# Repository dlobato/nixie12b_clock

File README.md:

# nixie12b_clock

This is just a simple project to build a clock using nixie displays. It's kind of a prototype to play with the nixies, although it's fully functional.

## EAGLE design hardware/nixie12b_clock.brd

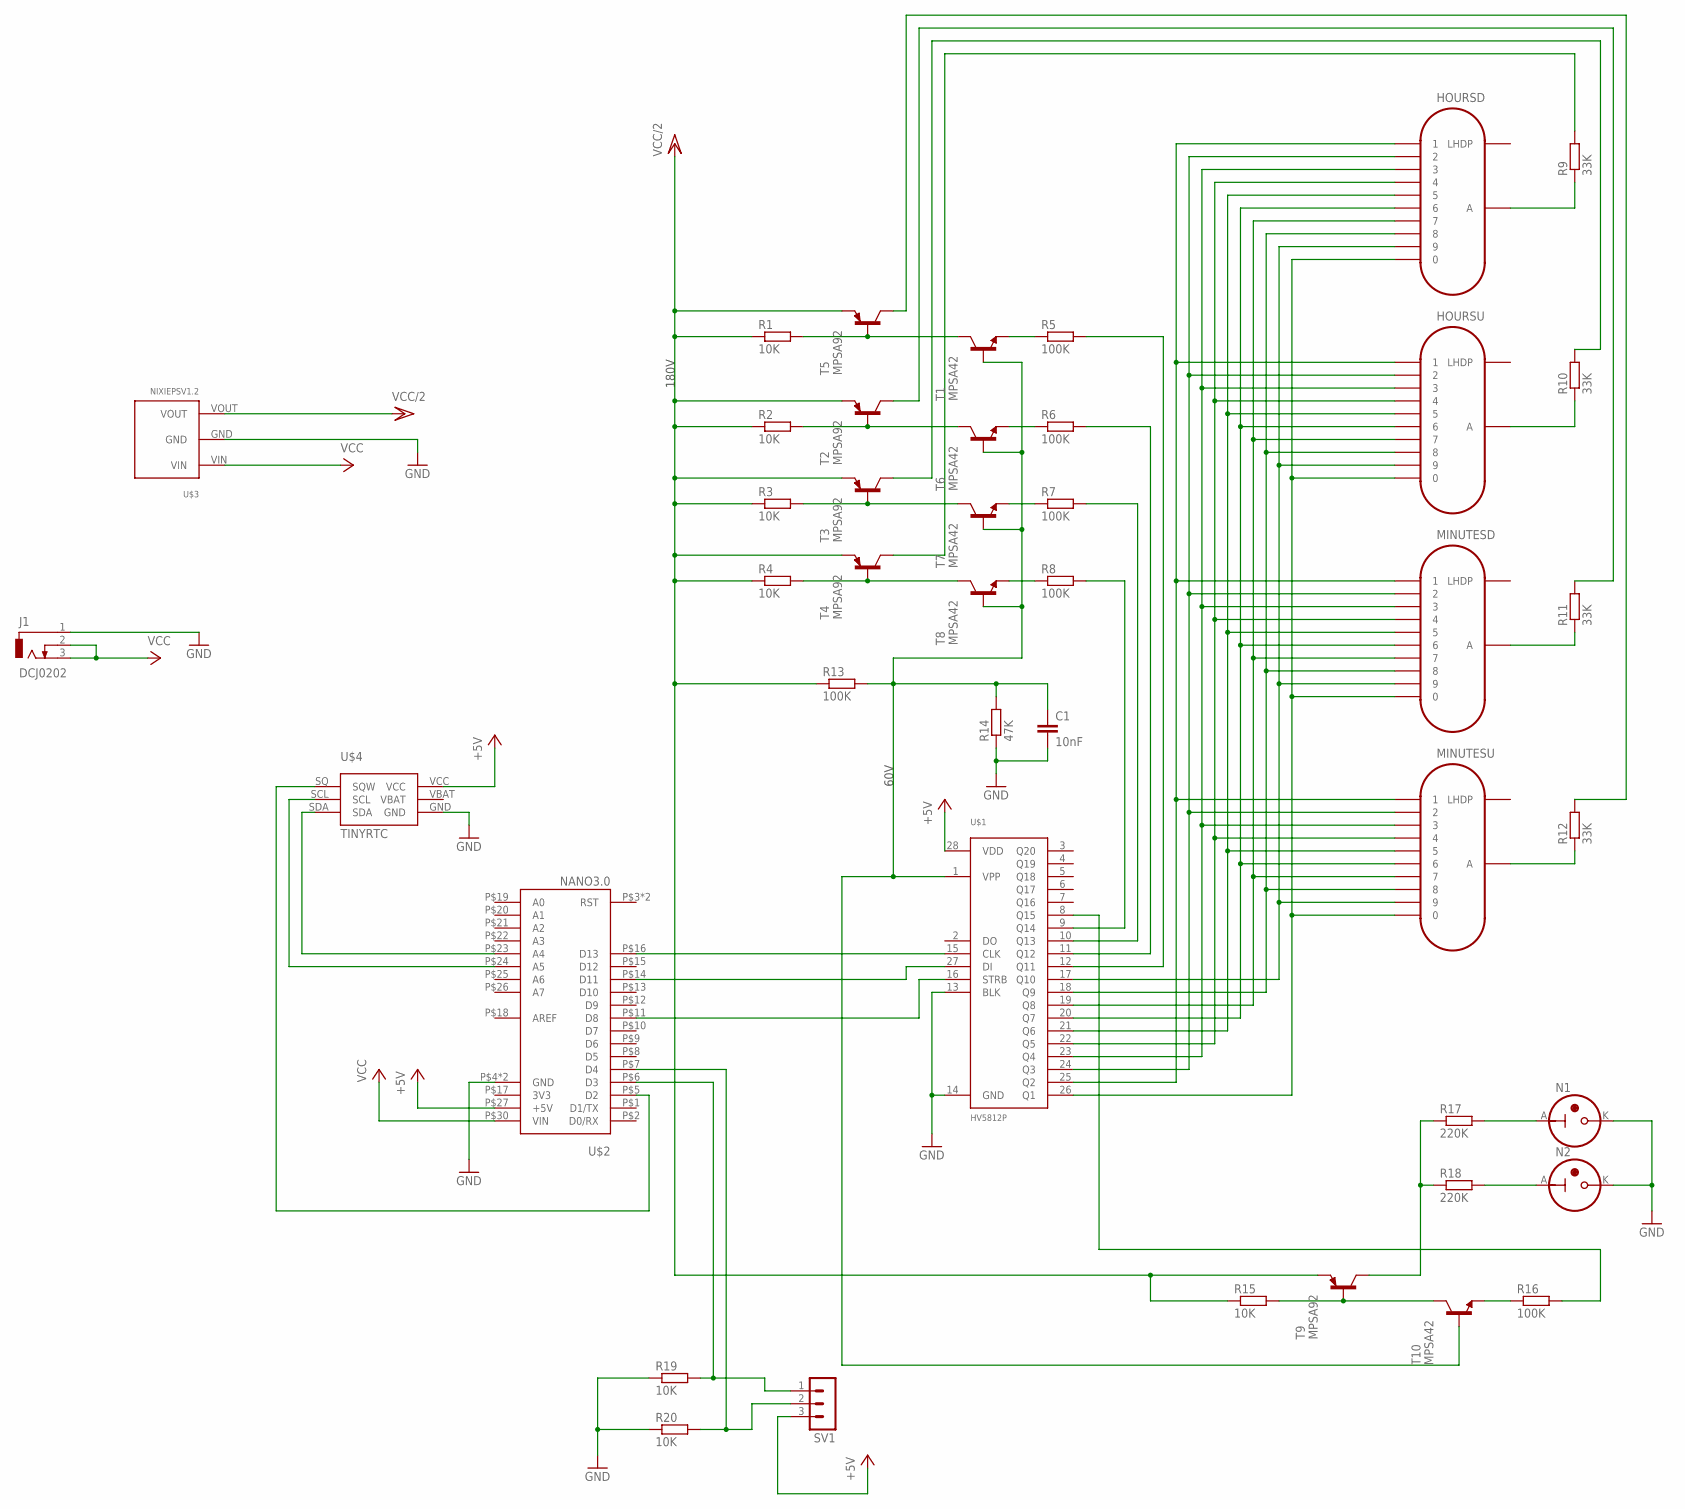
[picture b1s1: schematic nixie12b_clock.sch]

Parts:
C1: 10nF; C5B2.5
HOURSD: IN-12BP; IN-12-2
HOURSU: IN-12BP; IN-12-2
J1: DCJ0202
MINUTESD: IN-12BP; IN-12-2
MINUTESU: IN-12BP; IN-12-2
N1, N2: IN-3
R1, R2, R3, R4, R15, R19, R20: 10K; 0207/10
R5, R6, R7, R8, R13, R16: 100K; 0207/10
R9, R10, R11, R12: 33K; 0207/10
R14: 47K; 0207/10
R17, R18: 220K; 0207/10
SV1: MA03-1
T1, T6, T7, T8, T10: MPSA42; TO92-EBC
T2, T3, T4, T5, T9: MPSA92; TO92-EBC
U$1: HV5812P; 28-PDIP
U$2: NANO3.0; NANO3.0_HEADERS
U$3: NIXIEPSV1.2
U$4: TINYRTC

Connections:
3V3: U$2.P$17 (3V3)
+5V: SV1.3, U$1.28 (VDD), U$2.P$27 (+5V), U$4.VCC
GND: C1.2, J1.1, N1.K, N2.K, R14.1, R19.1, R20.1, U$1.13 (BLK), U$1.14 (GND), U$2.P$4 (GND), U$2.P$29 (GND), U$3.GND, U$4.GND
unnamed: HOURSD.1, HOURSU.1, MINUTESD.1, MINUTESU.1, U$1.25 (Q2)
unnamed: HOURSD.2, HOURSU.2, MINUTESD.2, MINUTESU.2, U$1.24 (Q3)
unnamed: HOURSD.3, HOURSU.3, MINUTESD.3, MINUTESU.3, U$1.23 (Q4)
unnamed: HOURSD.4, HOURSU.4, MINUTESD.4, MINUTESU.4, U$1.22 (Q5)
unnamed: HOURSD.5, HOURSU.5, MINUTESD.5, MINUTESU.5, U$1.21 (Q6)
unnamed: HOURSD.6, HOURSU.6, MINUTESD.6, MINUTESU.6, U$1.20 (Q7)
unnamed: HOURSD.7, HOURSU.7, MINUTESD.7, MINUTESU.7, U$1.19 (Q8)
unnamed: HOURSD.8, HOURSU.8, MINUTESD.8, MINUTESU.8, U$1.18 (Q9)
unnamed: HOURSD.9, HOURSU.9, MINUTESD.9, MINUTESU.9, U$1.17 (Q10)
unnamed: HOURSD.0, HOURSU.0, MINUTESD.0, MINUTESU.0, U$1.26 (Q1)
unnamed: R1.2, T1.C, T5.B
unnamed: R2.2, T2.B, T6.C
unnamed: R3.2, T3.B, T7.C
unnamed: R4.2, T4.B, T8.C
unnamed: R5.1, T1.E
unnamed: R6.1, T6.E
unnamed: R7.1, T7.E
unnamed: R8.1, T8.E
unnamed: C1.1, R13.2, R14.2, T1.B, T6.B, T7.B, T8.B, T10.B, U$1.1 (VPP)
unnamed: R5.2, U$1.12 (Q11)
unnamed: R6.2, U$1.11 (Q12)
unnamed: R7.2, U$1.10 (Q13)
unnamed: R8.2, U$1.9 (Q14)
unnamed: R9.2, T4.C
unnamed: HOURSD.A, R9.1
unnamed: R10.2, T3.C
unnamed: HOURSU.A, R10.1
unnamed: R11.2, T2.C
unnamed: MINUTESD.A, R11.1
unnamed: R12.2, T5.C
unnamed: MINUTESU.A, R12.1
unnamed: R15.2, T9.B, T10.C
unnamed: U$1.16 (STRB), U$2.P$11 (D8)
unnamed: U$1.27 (DI), U$2.P$14 (D11)
unnamed: U$1.15 (CLK), U$2.P$16 (D13)
unnamed: R19.2, SV1.1, U$2.P$6 (D3)
unnamed: R16.2, U$1.8 (Q15)
unnamed: R17.1, R18.1, T9.C
unnamed: R16.1, T10.E
unnamed: N1.A, R17.2
unnamed: N2.A, R18.2
unnamed: U$2.P$24 (A5), U$4.SCL
unnamed: U$2.P$23 (A4), U$4.SDA
unnamed: U$2.P$5 (D2), U$4.SQ (SQW)
unnamed: R20.2, SV1.2, U$2.P$7 (D4)
VBAT: U$4.VBAT
VCC: J1.2, J1.3, U$2.P$30 (VIN), U$3.VIN
VCC/2: R1.1, R2.1, R3.1, R4.1, R13.1, R15.1, T2.E, T3.E, T4.E, T5.E, T9.E, U$3.VOUT

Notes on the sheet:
60V
180V

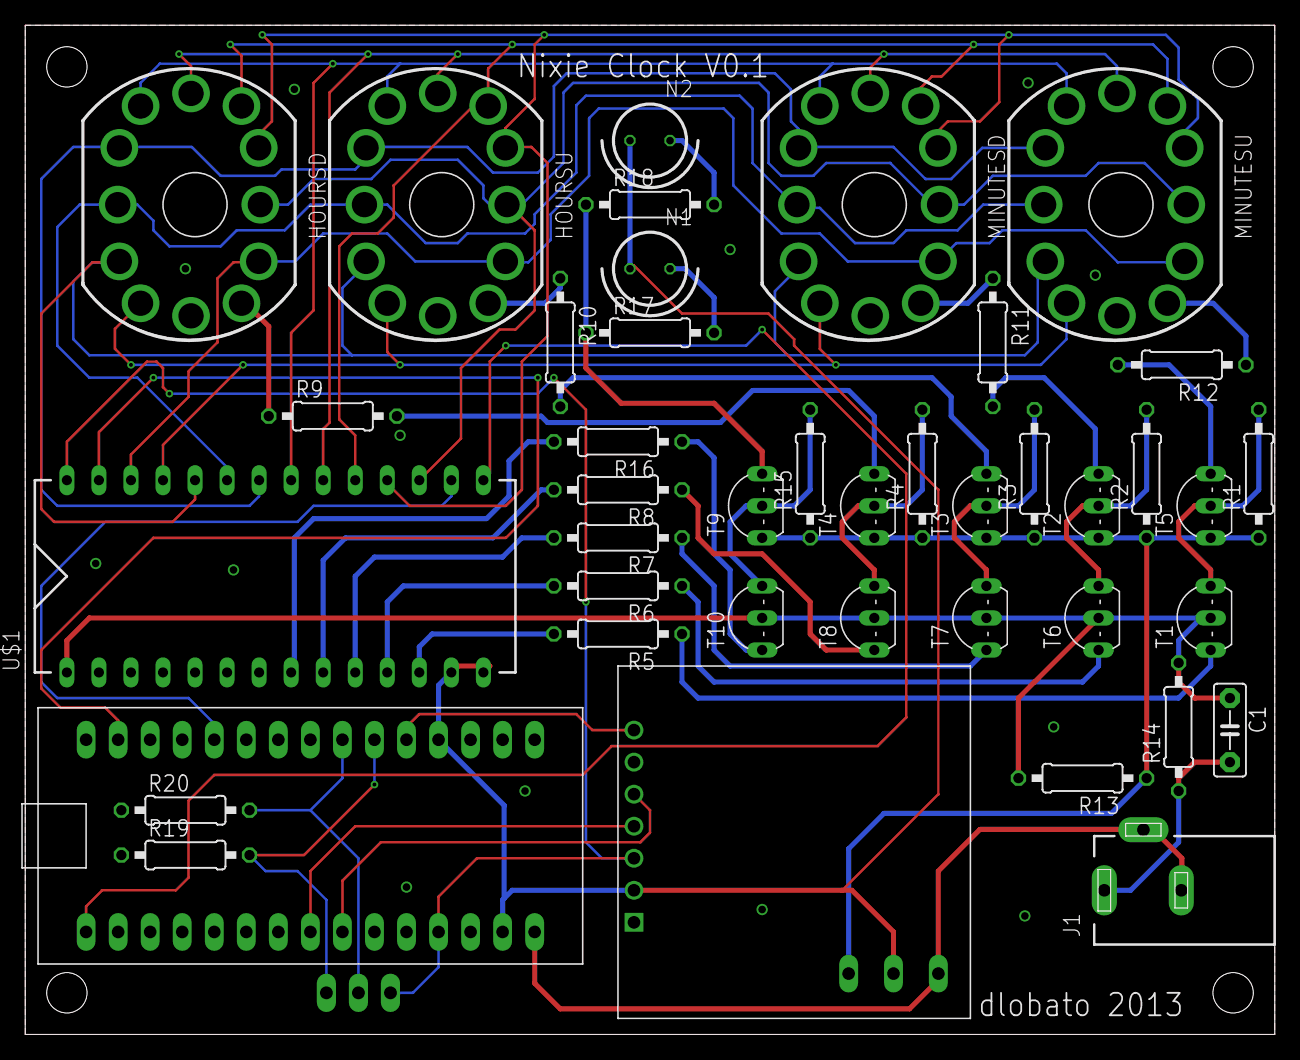
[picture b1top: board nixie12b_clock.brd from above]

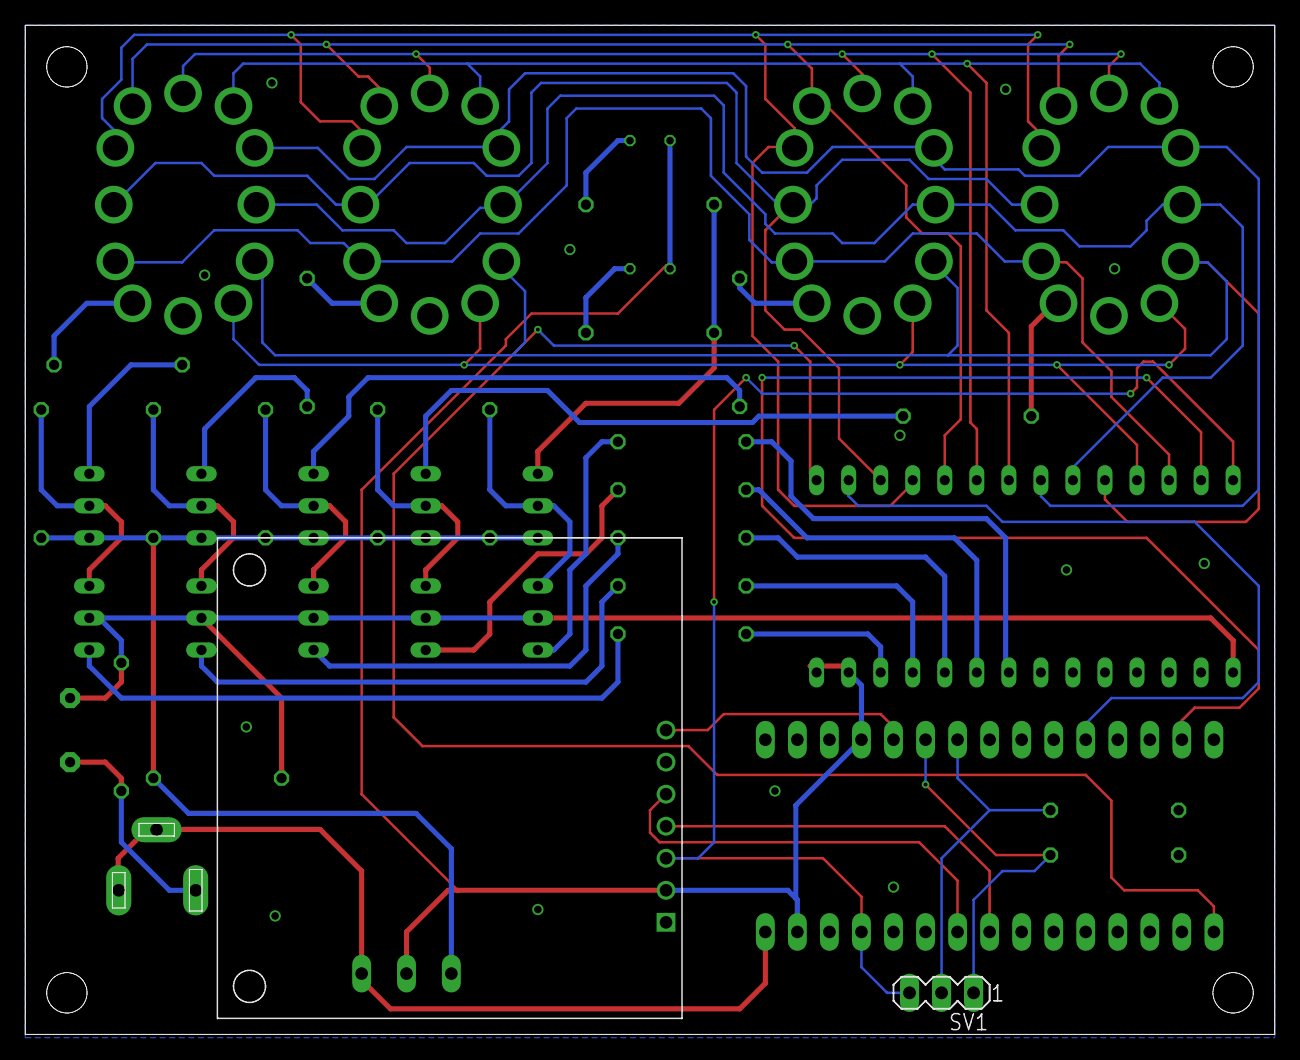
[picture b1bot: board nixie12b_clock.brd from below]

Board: 2 copper layers, 99.1 x 80.0 mm, 43 parts (2 on the bottom side), 49 nets.

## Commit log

2015-03-19 add project files to repository
2015-04-01 clean up timer1 code
2015-09-04 Changes for makerfaire
2015-09-04 Deleted backup files
2016-06-18 initial changes
2016-06-19 Moved serial begin to setup start
2017-04-19 removed unnedded libs. undated time libs. added button controls to setup time.
